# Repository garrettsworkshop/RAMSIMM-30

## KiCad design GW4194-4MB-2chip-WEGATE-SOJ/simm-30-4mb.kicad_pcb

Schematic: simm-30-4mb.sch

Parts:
C1, C2, C3, C4, C5, C6, C7, C8: 100n; C_0805
C9: 18p; C_0805
J1: DRAM-SIMM-30; SIMM-30_Edge
R1: EDO; R_0805
R2: FPM; R_0805
R3: 180; R_0805
R4: 33; R_0805
U1, U2: AS4C4M4; SOJ-24-26-300mil
U3: 74LVC1G04; SOT-353
U4: 74LVC1G74DC; NXP_TSSOP-8_3x3mm_P0.65mm
U5: 74LVC1G32; SOT-353
U6: XC6206PxxxMR; SOT-23

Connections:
+3V3: C6.1, C7.1, C8.1, U3.5, U4.7, U4.8, U5.5, U6.2
+5V: C1.1, C2.1, C3.1, C4.1, C5.1, J1.1, J1.30, U1.1, U1.13, U2.1, U2.13, U6.3
/1A0: J1.15, U1.9, U2.11
/1A1: J1.12, U1.10, U2.10
/1A2: J1.8, U1.11, U2.9
/1A3: J1.5, U1.12, U2.8
/1A4: J1.4, U1.15, U2.21
/1A5: J1.7, U1.16, U2.19
/1A6: J1.11, U1.17, U2.18
/1A7: J1.14, U1.18, U2.17
/1A8: J1.17, U1.19, U2.16
/1A9: J1.19, U1.21, U2.15
/1A10: J1.18, U1.8, U2.12
/A11: J1.24
/D0: J1.3, U2.25
/D1: J1.6, U2.2
/D2: J1.10, U2.24
/D3: J1.13, U2.3
/D4: J1.16, U1.25
/D5: J1.20, U1.2
/D6: J1.23, U1.24
/D7: J1.25, U1.3
/DP: J1.29
/QP: J1.26
/~CASP~: J1.28
/~CAS~: J1.2, R1.1, U1.23, U2.23, U4.2
/~OE~: R1.2, R2.1, U1.22, U2.22
/~RAS~: J1.27, U1.5, U2.5, U3.2
/~RWE~: R4.1, U1.4, U2.4
/~WEE~: U4.3, U5.2
/~WE~: J1.21, U5.1
GND: C1.2, C2.2, C3.2, C4.2, C5.2, C6.2, C7.2, C8.2, C9.2, J1.9, J1.22, R2.2, U1.14, U1.26, U2.14, U2.26, U3.3, U4.4, U5.3, U6.1
unnamed: C9.1, R3.1, U4.1
unnamed: R3.2, U3.4, U4.6
unnamed: R4.2, U5.4

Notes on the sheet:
1-5ns delay
1-3ns delay
1-6ns delay
1-4ns delay

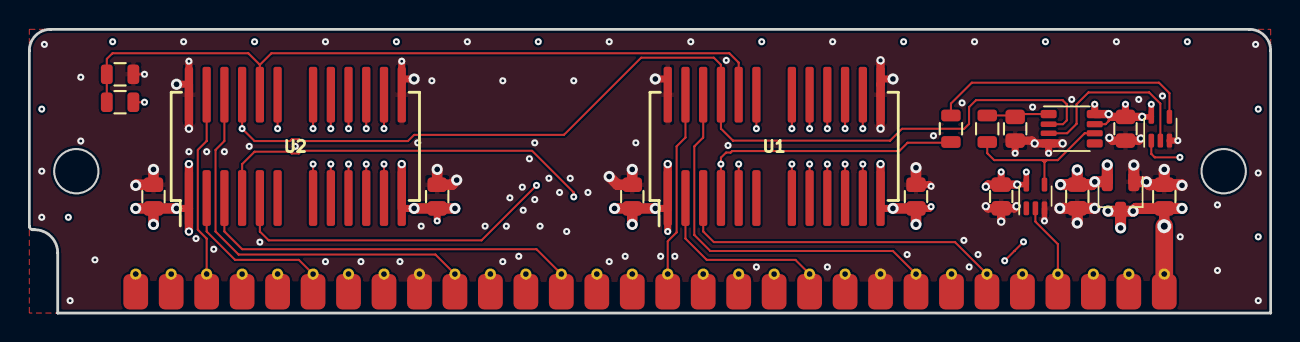
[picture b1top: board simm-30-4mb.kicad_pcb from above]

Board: 4 copper layers, 88.9 x 20.3 mm, 20 parts (0 on the bottom side), 31 nets.
